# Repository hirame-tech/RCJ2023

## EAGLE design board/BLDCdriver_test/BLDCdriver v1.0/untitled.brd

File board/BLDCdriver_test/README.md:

## issue v1.0
- 1.SPIのSSの未配線
→~~CSをMD基板側でGNDに落として解決(v1.1)~~→SSをD6に配線
- 2.電源コネクタの配線が逆 → 元に戻した(v1.1)

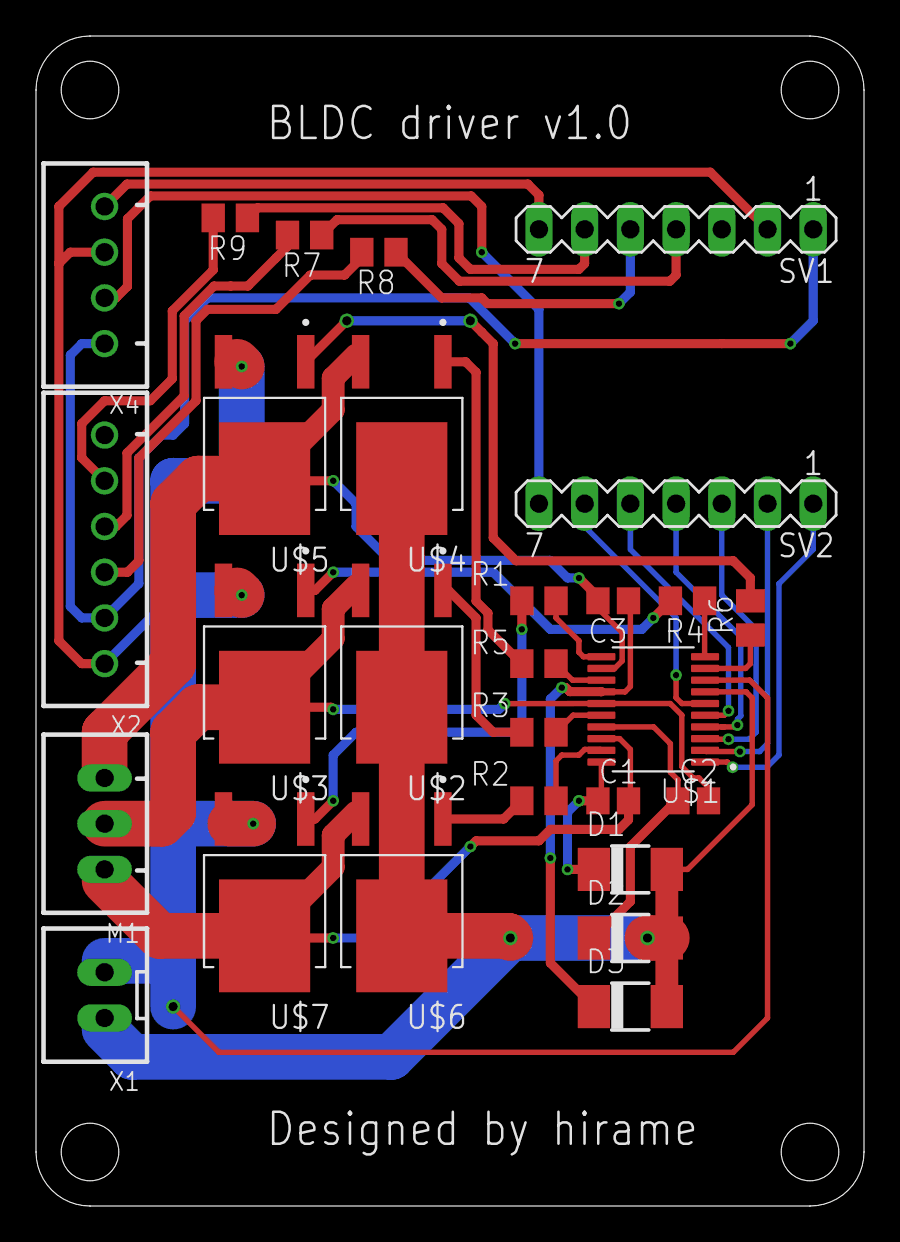
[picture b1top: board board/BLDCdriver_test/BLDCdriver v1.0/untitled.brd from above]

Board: 2 copper layers, 46.0 x 65.0 mm, 28 parts (0 on the bottom side), 35 nets.

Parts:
C1, C2, C3: 1uF; C2012
D1, D2, D3: DO-214AC
M1: JST-XH-03-PIN-LONG-PAD; JST-XH-03-PACKAGE-LONG-PAD
R1, R2, R3, R4, R5, R6: M2012
R7, R8, R9: 300Ω; M2012
SV1, SV2: MA07-1
U$1: DRV8300NIPWR; SOIC65P640X120-20N
U$2, U$3, U$4, U$5, U$6, U$7: H-CHMOSFET; DPAK228P990X238-4N
X1: JST-XH-02-PIN-LONG-PAD; JST-XH-02-PACKAGE-LONG-PAD
X2: JST-XH-06-PIN-ROUND-PAD; JST-XH-06-PACKAGE-ROUND-PAD
X4: JST-XH-04-PIN-ROUND-PAD; JST-XH-04-PACKAGE-ROUND-PAD

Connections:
+5V: SV1.1, X2.2, X4.1
GND: SV1.2, U$1.8, U$3.3, U$5.3, U$7.3, X1.2, X2.1, X4.3
HA: SV2.1, U$1.1
HB: SV2.2, U$1.2
HC: SV2.3, U$1.3
LA: SV2.4, U$1.4
LB: SV2.5, U$1.5
LC: SV2.6, U$1.6
MISO: R8.2, X2.3
MOSI: R7.2, X2.4
unnamed: C2.2, M1.2, U$1.15, U$2.3, U$3.4
unnamed: C3.2, M1.3, U$1.12, U$4.3, U$5.4
unnamed: C1.2, M1.1, U$1.18, U$6.3, U$7.4
unnamed: R2.2, U$6.1
unnamed: R1.2, U$7.1
unnamed: R2.1, U$1.19
unnamed: R1.1, U$1.11
unnamed: R3.2, U$2.1
unnamed: C1.1, D1.C, U$1.20
unnamed: R4.2, U$3.1
unnamed: R7.1, SV1.4
unnamed: R3.1, U$1.16
unnamed: C2.1, D2.C, U$1.17
unnamed: R4.1, U$1.10
unnamed: R6.2, U$5.1
unnamed: R5.2, U$4.1
unnamed: R5.1, U$1.13
unnamed: R6.1, U$1.9
unnamed: C3.1, D3.C, U$1.14
unnamed: R9.1, SV1.6
unnamed: R8.1, SV1.5
RX: SV1.7, X4.4
SCK: R9.2, X2.5
TX: SV2.7, X4.2
VCC: D1.A, D2.A, D3.A, U$1.7, U$2.4, U$4.4, U$6.4, X1.1

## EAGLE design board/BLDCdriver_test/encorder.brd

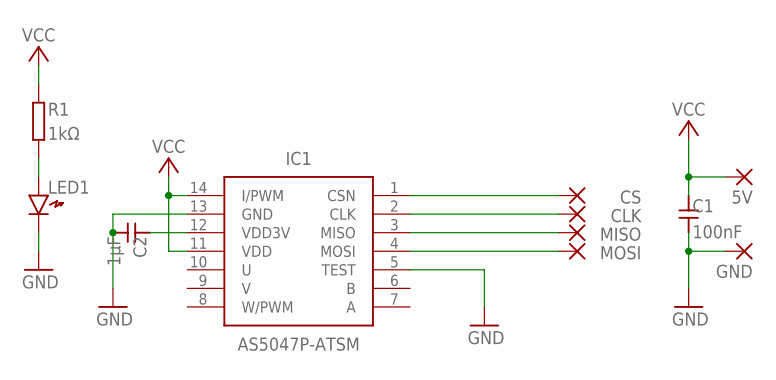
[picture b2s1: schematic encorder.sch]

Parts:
5V: SMD2; SMD1,27-2,54
C1: 100nF; SMD1608
C2: 1µF; SMD1608
CLK: SMD2; SMD1,27-2,54
CS: SMD2; SMD1,27-2,54
GND: SMD2; SMD1,27-2,54
IC1: AS5047P-ATSM; SOP65P640X120-14N
LED1: LED1608
MISO: SMD2; SMD1,27-2,54
MOSI: SMD2; SMD1,27-2,54
R1: 1kΩ; SMD1608

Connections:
GND: C1.2, C2.2, GND.1, IC1.5 (TEST), IC1.13 (GND), LED1.K
unnamed: C2.1, IC1.12 (VDD3V)
unnamed: CS.1, IC1.1 (CSN)
unnamed: CLK.1, IC1.2 (CLK)
unnamed: IC1.3 (MISO), MISO.1
unnamed: IC1.4 (MOSI), MOSI.1
unnamed: LED1.A, R1.2
VCC: 5V.1, C1.1, IC1.11 (VDD), IC1.14 (I/PWM), R1.1

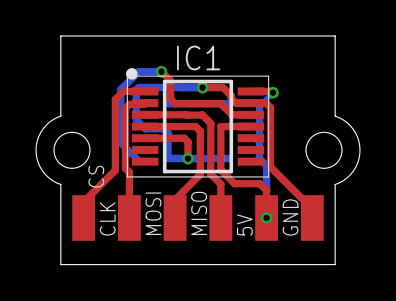
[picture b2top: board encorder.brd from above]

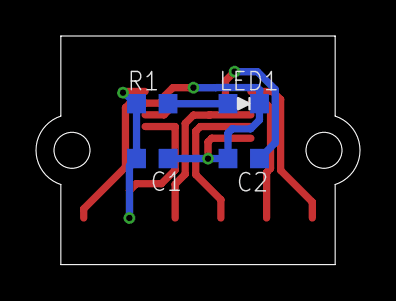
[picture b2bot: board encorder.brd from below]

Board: 2 copper layers, 18.0 x 12.7 mm, 11 parts (4 on the bottom side), 8 nets.

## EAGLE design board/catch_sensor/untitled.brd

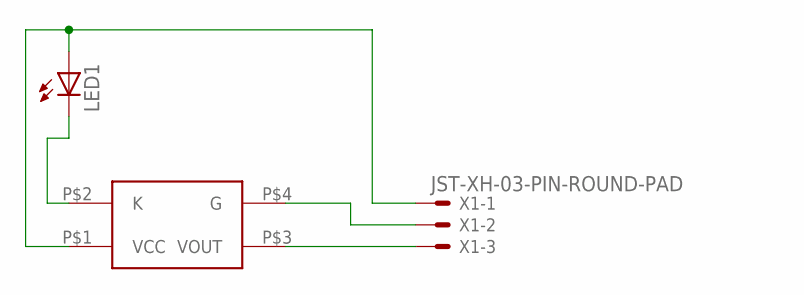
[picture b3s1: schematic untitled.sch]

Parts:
LED1: LED3MM
U$1: S4282-51
X1: JST-XH-03-PIN-ROUND-PAD; JST-XH-03-PACKAGE-ROUND-PAD

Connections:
unnamed: LED1.K (C), U$1.P$2 (K)
unnamed: U$1.P$3 (VOUT), X1.3
unnamed: LED1.A, U$1.P$1 (VCC), X1.1
unnamed: U$1.P$4 (G), X1.2

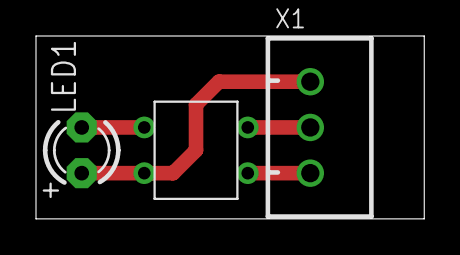
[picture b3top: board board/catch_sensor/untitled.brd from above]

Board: 2 copper layers, 21.6 x 10.2 mm, 3 parts (0 on the bottom side), 4 nets.

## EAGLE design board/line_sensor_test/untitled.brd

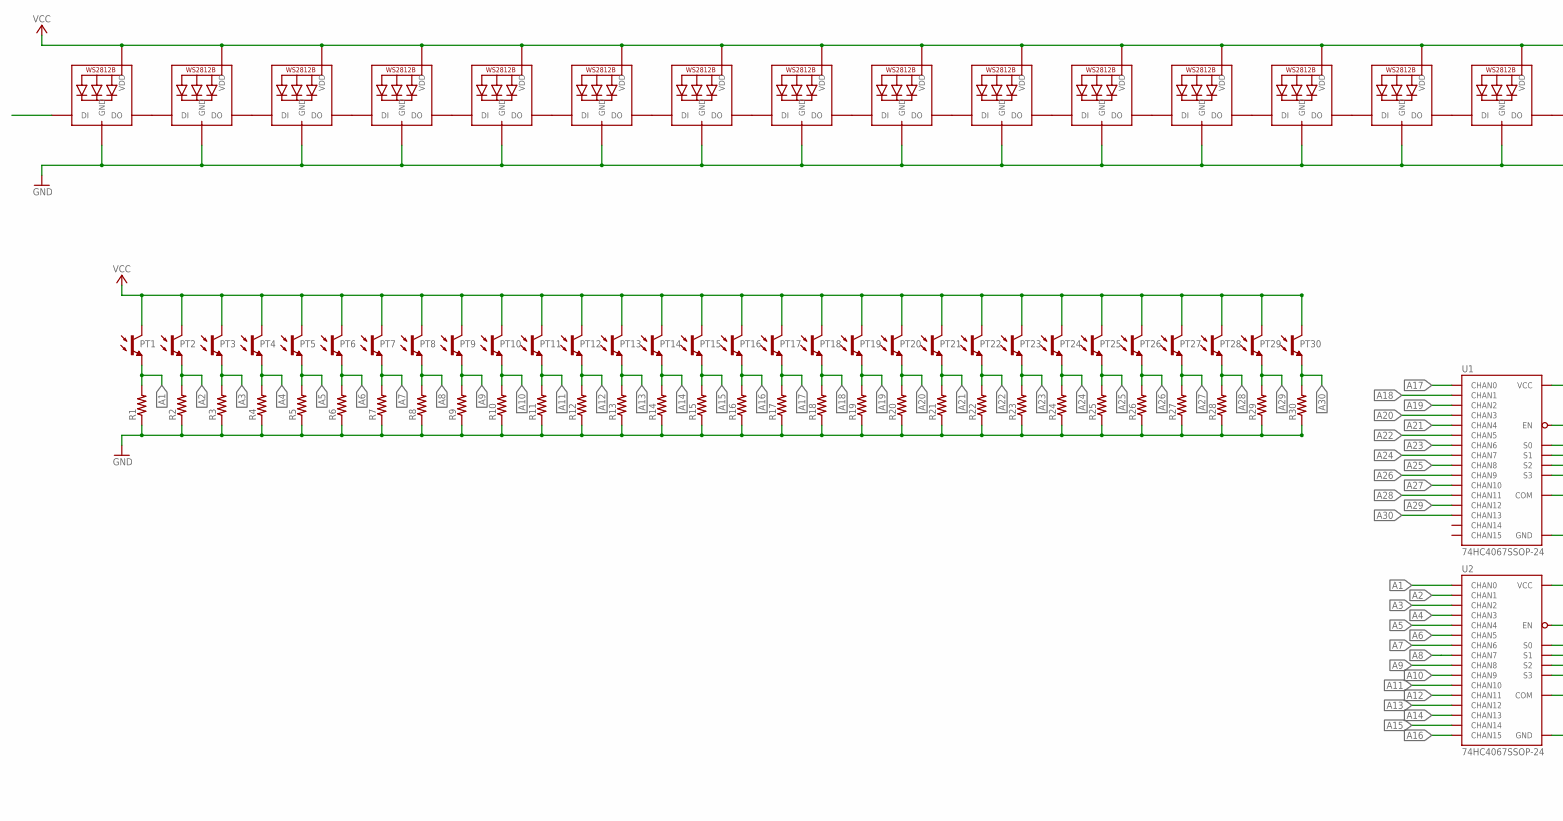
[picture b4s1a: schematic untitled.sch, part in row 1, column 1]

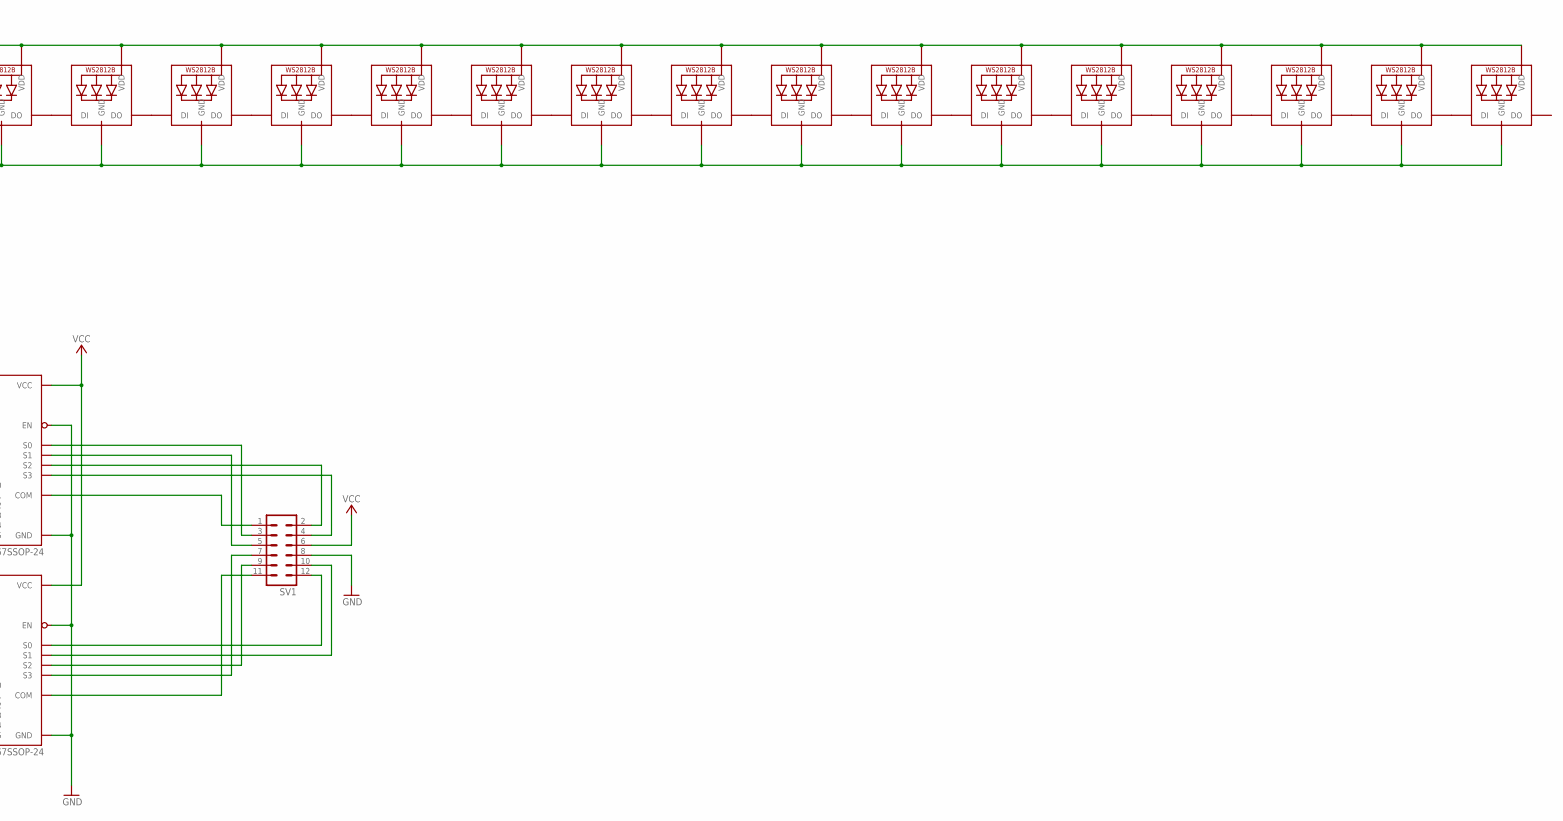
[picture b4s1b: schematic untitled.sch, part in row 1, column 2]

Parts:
LED1, LED2, LED3, LED4, LED5, LED6, LED7, LED8, LED9, LED10, LED11, LED12, LED13, LED14, LED15, LED16, LED17, LED18, LED19, LED20, LED21, LED22, LED23, LED24, LED25, LED26, LED27, LED28, LED29, LED30: WS2812B_5050N; WS2812B-NARROW
PT1, PT2, PT3, PT4, PT5, PT6, PT7, PT8, PT9, PT10, PT11, PT12, PT13, PT14, PT15, PT16, PT17, PT18, PT19, PT20, PT21, PT22, PT23, PT24, PT25, PT26, PT27, PT28, PT29, PT30: TPS611; NJL7502L
R1, R2, R3, R4, R5, R6, R7, R8, R9, R10, R11, R12, R13, R14, R15, R16, R17, R18, R19, R20, R21, R22, R23, R24, R25, R26, R27, R28, R29, R30: R-US_M2012; M2012
SV1: MA06-2
U1, U2: 74HC4067SSOP-24; SSOP24

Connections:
A1: PT1.E, R1.2, U2.9 (CHAN0)
A2: PT2.E, R2.2, U2.8 (CHAN1)
A3: PT3.E, R3.2, U2.7 (CHAN2)
A4: PT4.E, R4.2, U2.6 (CHAN3)
A5: PT5.E, R5.2, U2.5 (CHAN4)
A6: PT6.E, R6.2, U2.4 (CHAN5)
A7: PT7.E, R7.2, U2.3 (CHAN6)
A8: PT8.E, R8.2, U2.2 (CHAN7)
A9: PT9.E, R9.2, U2.23 (CHAN8)
A10: PT10.E, R10.2, U2.22 (CHAN9)
A11: PT11.E, R11.2, U2.21 (CHAN10)
A12: PT12.E, R12.2, U2.20 (CHAN11)
A13: PT13.E, R13.2, U2.19 (CHAN12)
A14: PT14.E, R14.2, U2.18 (CHAN13)
A15: PT15.E, R15.2, U2.17 (CHAN14)
A16: PT16.E, R16.2, U2.16 (CHAN15)
A17: PT17.E, R17.2, U1.9 (CHAN0)
A18: PT18.E, R18.2, U1.8 (CHAN1)
A19: PT19.E, R19.2, U1.7 (CHAN2)
A20: PT20.E, R20.2, U1.6 (CHAN3)
A21: PT21.E, R21.2, U1.5 (CHAN4)
A22: PT22.E, R22.2, U1.4 (CHAN5)
A23: PT23.E, R23.2, U1.3 (CHAN6)
A24: PT24.E, R24.2, U1.2 (CHAN7)
A25: PT25.E, R25.2, U1.23 (CHAN8)
A26: PT26.E, R26.2, U1.22 (CHAN9)
A27: PT27.E, R27.2, U1.21 (CHAN10)
A28: PT28.E, R28.2, U1.20 (CHAN11)
A29: PT29.E, R29.2, U1.19 (CHAN12)
A30: PT30.E, R30.2, U1.18 (CHAN13)
AIN0: SV1.1, U1.1 (COM); also elsewhere on the board
AIN1: SV1.11, U2.1 (COM); also elsewhere on the board
GND: LED1.3-GND (GND), LED2.3-GND (GND), LED3.3-GND (GND), LED4.3-GND (GND), LED5.3-GND (GND), LED6.3-GND (GND), LED7.3-GND (GND), LED8.3-GND (GND), LED9.3-GND (GND), LED10.3-GND (GND), LED11.3-GND (GND), LED12.3-GND (GND), LED13.3-GND (GND), LED14.3-GND (GND), LED15.3-GND (GND), LED16.3-GND (GND), LED17.3-GND (GND), LED18.3-GND (GND), LED19.3-GND (GND), LED20.3-GND (GND), LED21.3-GND (GND), LED22.3-GND (GND), LED23.3-GND (GND), LED24.3-GND (GND), LED25.3-GND (GND), LED26.3-GND (GND), LED27.3-GND (GND), LED28.3-GND (GND), LED29.3-GND (GND), LED30.3-GND (GND), R1.1, R2.1, R3.1, R4.1, R5.1, R6.1, R7.1, R8.1, R9.1, R10.1, R11.1, R12.1, R13.1, R14.1, R15.1, R16.1, R17.1, R18.1, R19.1, R20.1, R21.1, R22.1, R23.1, R24.1, R25.1, R26.1, R27.1, R28.1, R29.1, R30.1, SV1.8, U1.12 (GND), U1.15 (EN), U2.12 (GND), U2.15 (EN); also elsewhere on the board
LED_IN: LED1.4-DIN (DI); also elsewhere on the board
LED_OUT: LED30.2-DOUT (DO); also elsewhere on the board
unnamed: LED1.2-DOUT (DO), LED2.4-DIN (DI)
unnamed: LED2.2-DOUT (DO), LED3.4-DIN (DI)
unnamed: LED3.2-DOUT (DO), LED4.4-DIN (DI)
unnamed: LED4.2-DOUT (DO), LED5.4-DIN (DI)
unnamed: LED6.2-DOUT (DO), LED7.4-DIN (DI)
unnamed 40: SV1.2, U1.14 (S2); also elsewhere on the board
unnamed 41: SV1.4, U1.13 (S3); also elsewhere on the board
unnamed 42: SV1.7, U2.13 (S3); also elsewhere on the board
unnamed 43: SV1.9, U2.14 (S2); also elsewhere on the board
unnamed: LED7.2-DOUT (DO), LED8.4-DIN (DI)
unnamed 45: SV1.10, U2.11 (S1); also elsewhere on the board
unnamed 46: SV1.12, U2.10 (S0); also elsewhere on the board
unnamed 47: SV1.5, U1.11 (S1); also elsewhere on the board
unnamed 48: SV1.3, U1.10 (S0); also elsewhere on the board
unnamed: LED8.2-DOUT (DO), LED9.4-DIN (DI)
unnamed: LED9.2-DOUT (DO), LED10.4-DIN (DI)
unnamed: LED5.2-DOUT (DO), LED6.4-DIN (DI)
unnamed: LED11.2-DOUT (DO), LED12.4-DIN (DI)
unnamed: LED12.2-DOUT (DO), LED13.4-DIN (DI)
unnamed: LED13.2-DOUT (DO), LED14.4-DIN (DI)
unnamed: LED14.2-DOUT (DO), LED15.4-DIN (DI)
unnamed: LED10.2-DOUT (DO), LED11.4-DIN (DI)
unnamed: LED16.2-DOUT (DO), LED17.4-DIN (DI)
unnamed: LED17.2-DOUT (DO), LED18.4-DIN (DI)
unnamed: LED18.2-DOUT (DO), LED19.4-DIN (DI)
unnamed: LED19.2-DOUT (DO), LED20.4-DIN (DI)
unnamed: LED15.2-DOUT (DO), LED16.4-DIN (DI)
unnamed: LED21.2-DOUT (DO), LED22.4-DIN (DI)
unnamed: LED22.2-DOUT (DO), LED23.4-DIN (DI)
unnamed: LED23.2-DOUT (DO), LED24.4-DIN (DI)
unnamed: LED24.2-DOUT (DO), LED25.4-DIN (DI)
unnamed: LED20.2-DOUT (DO), LED21.4-DIN (DI)
unnamed: LED26.2-DOUT (DO), LED27.4-DIN (DI)
unnamed: LED27.2-DOUT (DO), LED28.4-DIN (DI)
unnamed: LED28.2-DOUT (DO), LED29.4-DIN (DI)
unnamed: LED29.2-DOUT (DO), LED30.4-DIN (DI)
unnamed: LED25.2-DOUT (DO), LED26.4-DIN (DI)
VCC: LED1.1-VDD (VDD), LED2.1-VDD (VDD), LED3.1-VDD (VDD), LED4.1-VDD (VDD), LED5.1-VDD (VDD), LED6.1-VDD (VDD), LED7.1-VDD (VDD), LED8.1-VDD (VDD), LED9.1-VDD (VDD), LED10.1-VDD (VDD), LED11.1-VDD (VDD), LED12.1-VDD (VDD), LED13.1-VDD (VDD), LED14.1-VDD (VDD), LED15.1-VDD (VDD), LED16.1-VDD (VDD), LED17.1-VDD (VDD), LED18.1-VDD (VDD), LED19.1-VDD (VDD), LED20.1-VDD (VDD), LED21.1-VDD (VDD), LED22.1-VDD (VDD), LED23.1-VDD (VDD), LED24.1-VDD (VDD), LED25.1-VDD (VDD), LED26.1-VDD (VDD), LED27.1-VDD (VDD), LED28.1-VDD (VDD), LED29.1-VDD (VDD), LED30.1-VDD (VDD), PT1.C, PT2.C, PT3.C, PT4.C, PT5.C, PT6.C, PT7.C, PT8.C, PT9.C, PT10.C, PT11.C, PT12.C, PT13.C, PT14.C, PT15.C, PT16.C, PT17.C, PT18.C, PT19.C, PT20.C, PT21.C, PT22.C, PT23.C, PT24.C, PT25.C, PT26.C, PT27.C, PT28.C, PT29.C, PT30.C, SV1.6, U1.24 (VCC), U2.24 (VCC); also elsewhere on the board

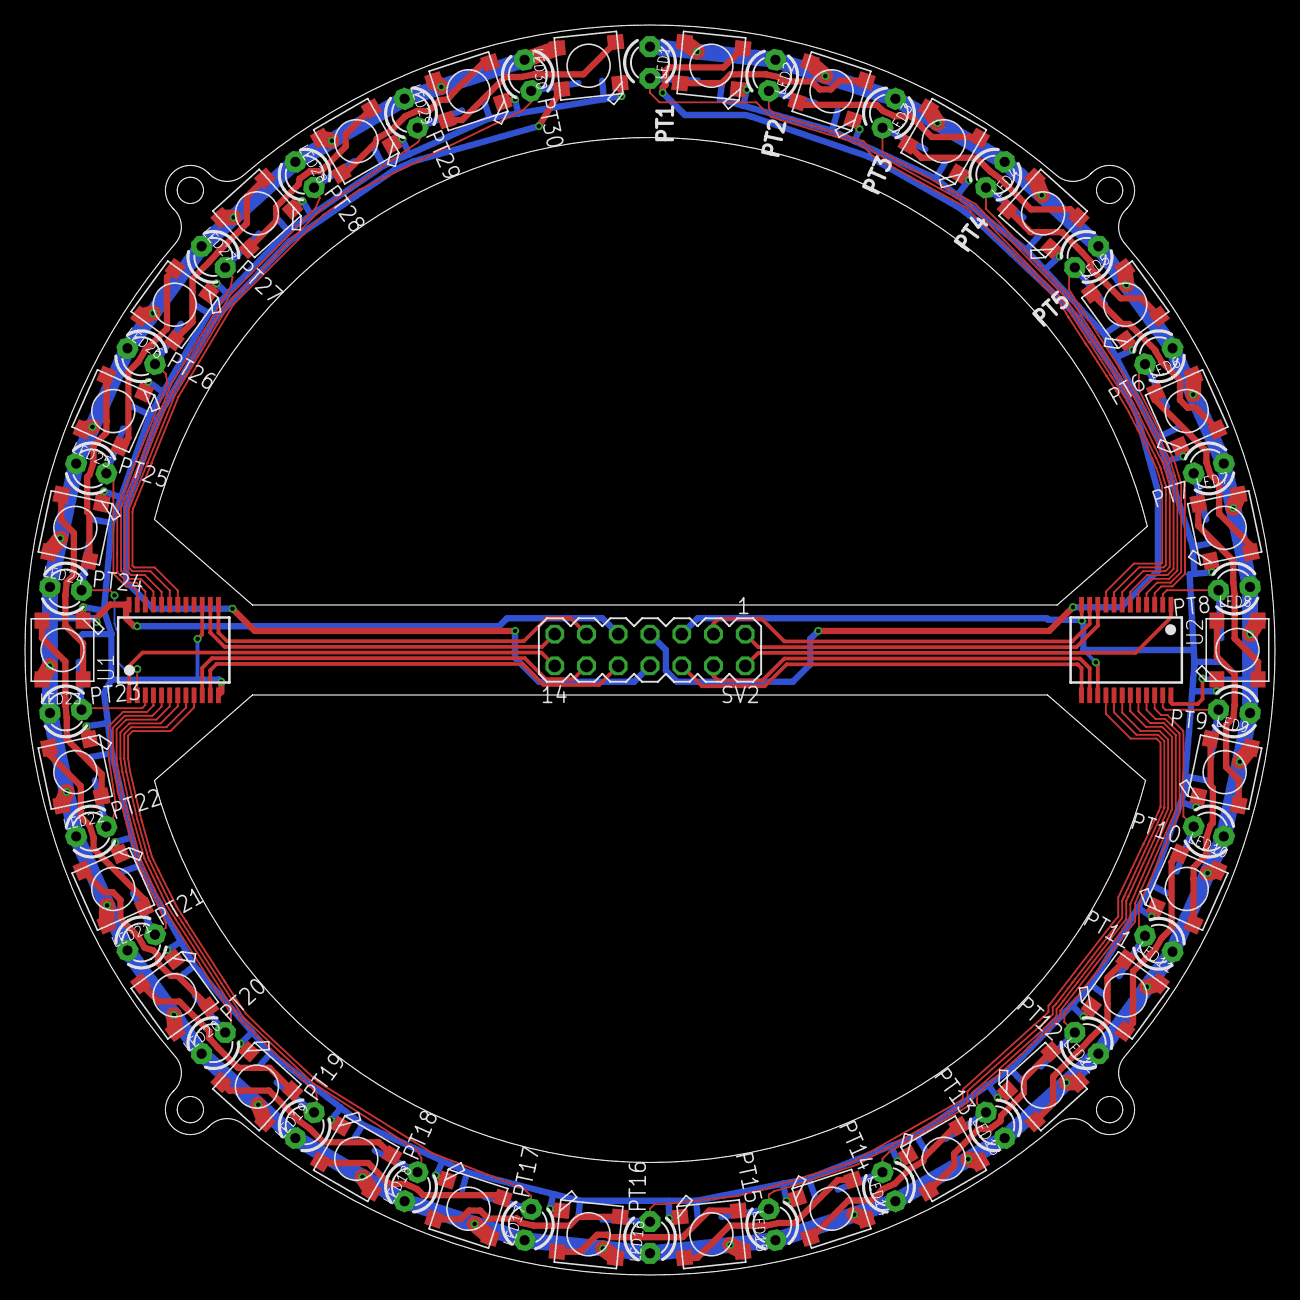
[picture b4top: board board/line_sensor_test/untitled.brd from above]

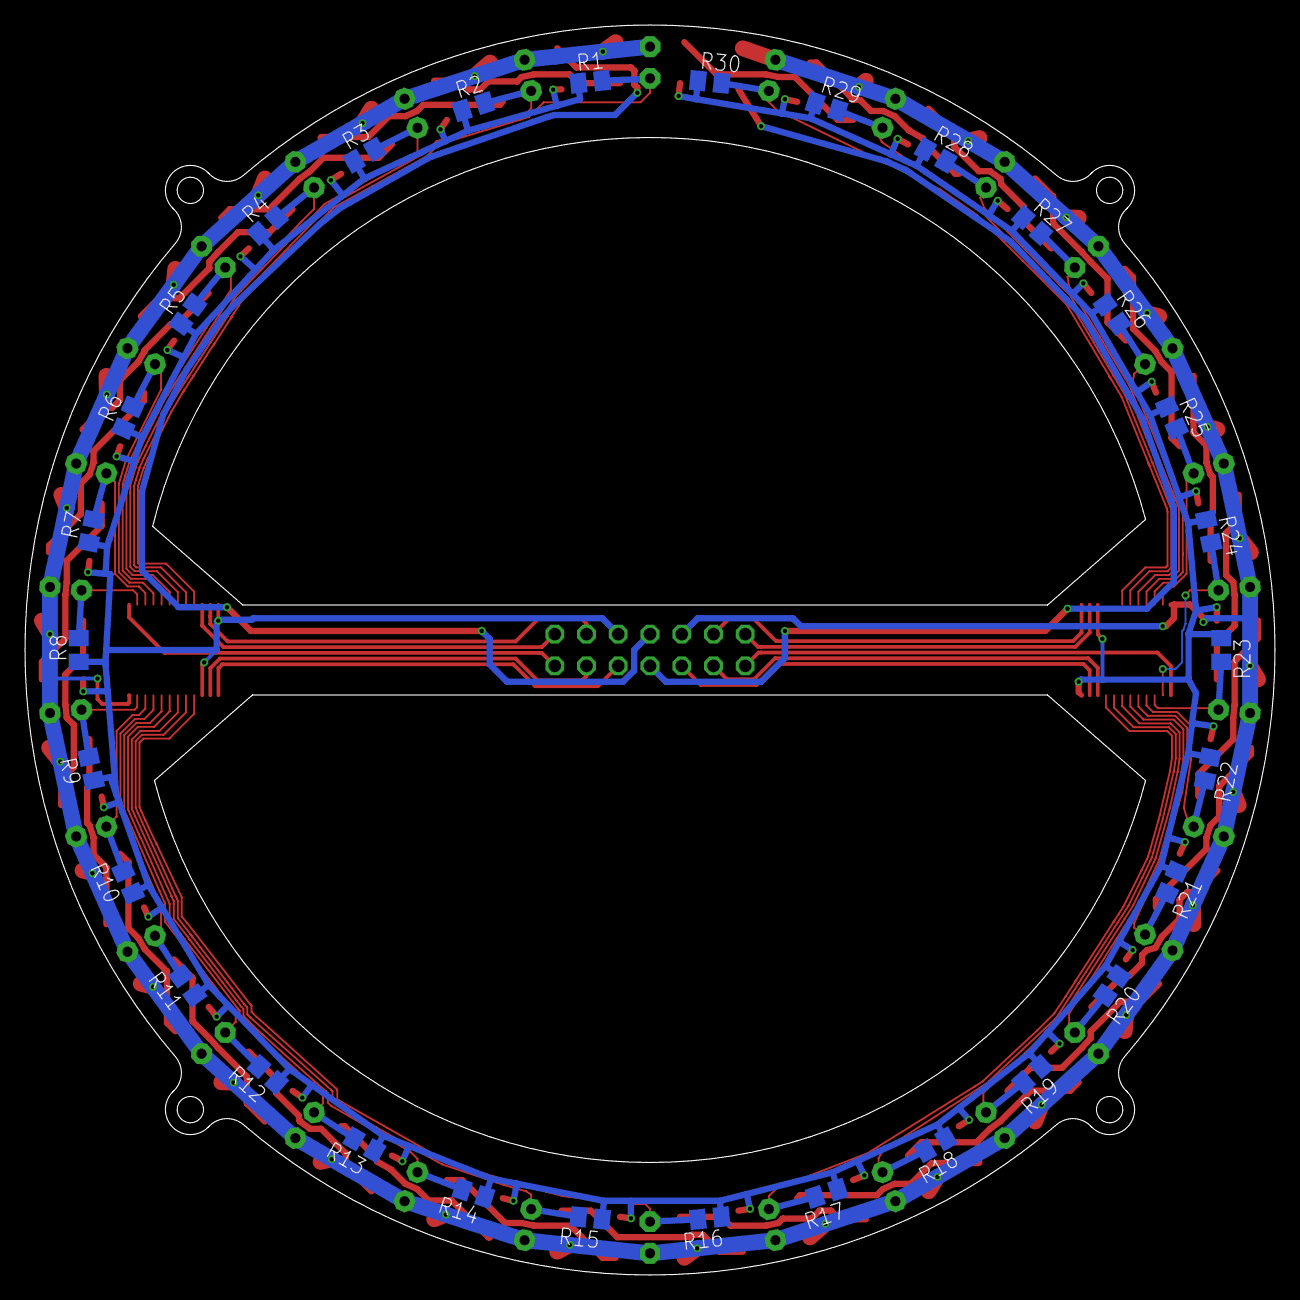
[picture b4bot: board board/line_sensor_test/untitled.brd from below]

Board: 2 copper layers, 100.0 x 100.0 mm, 93 parts (30 on the bottom side), 73 nets.

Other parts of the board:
SV2: MA07-2

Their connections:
AIN0: SV2.14; also elsewhere on the board
AIN1: SV2.2; also elsewhere on the board
GND: SV2.5; also elsewhere on the board
LED_IN: SV2.7; also elsewhere on the board
LED_OUT: SV2.8; also elsewhere on the board
unnamed 40: SV2.13; also elsewhere on the board
unnamed 41: SV2.11; also elsewhere on the board
unnamed 42: SV2.6; also elsewhere on the board
unnamed 43: SV2.4; also elsewhere on the board
unnamed 45: SV2.3; also elsewhere on the board
unnamed 46: SV2.1; also elsewhere on the board
unnamed 47: SV2.10; also elsewhere on the board
unnamed 48: SV2.12; also elsewhere on the board
VCC: SV2.9; also elsewhere on the board

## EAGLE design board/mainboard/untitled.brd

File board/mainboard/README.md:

#v1 isuue
 - RCフィルタのコンデンサがin側についている(out側にないといけない)

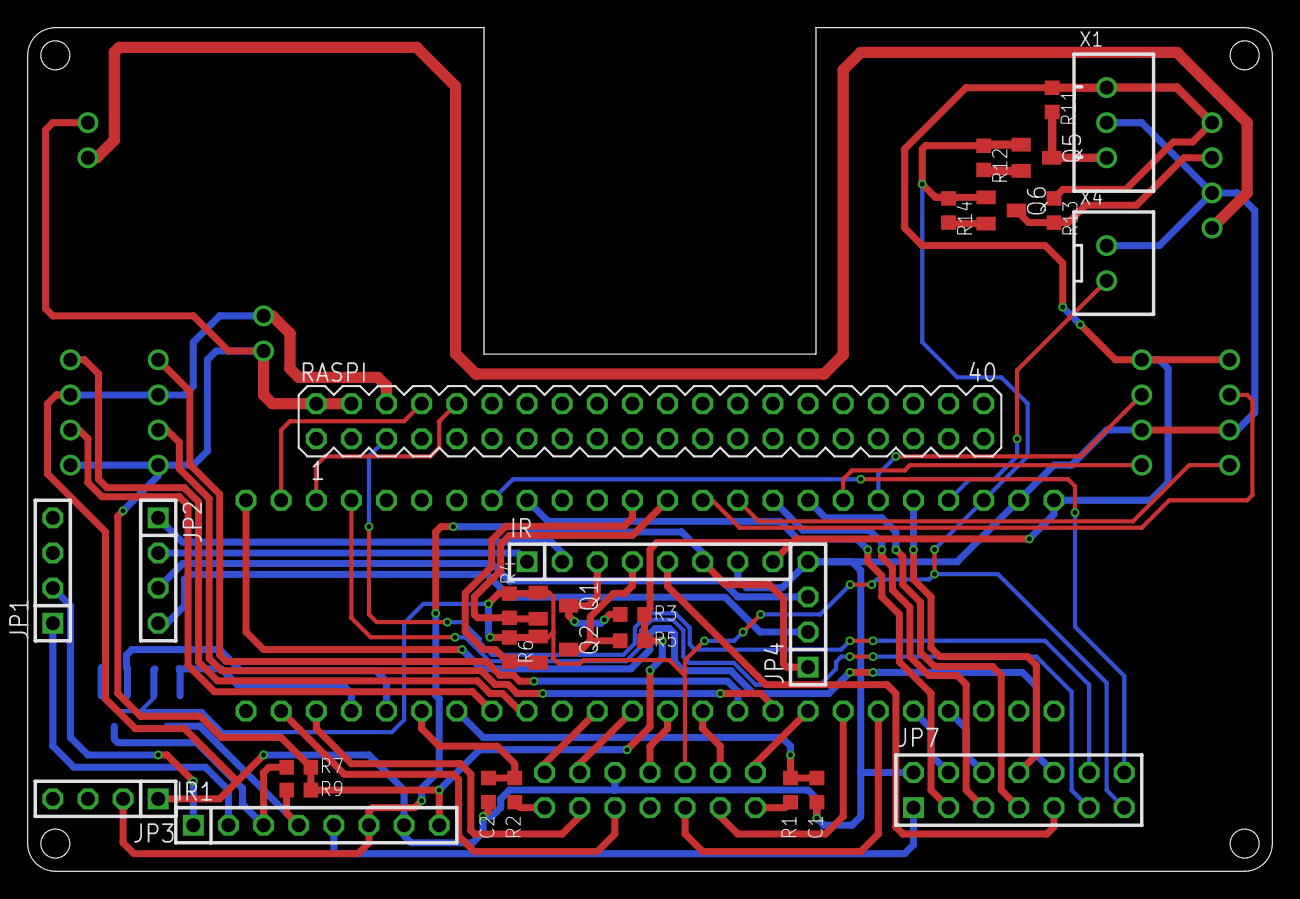
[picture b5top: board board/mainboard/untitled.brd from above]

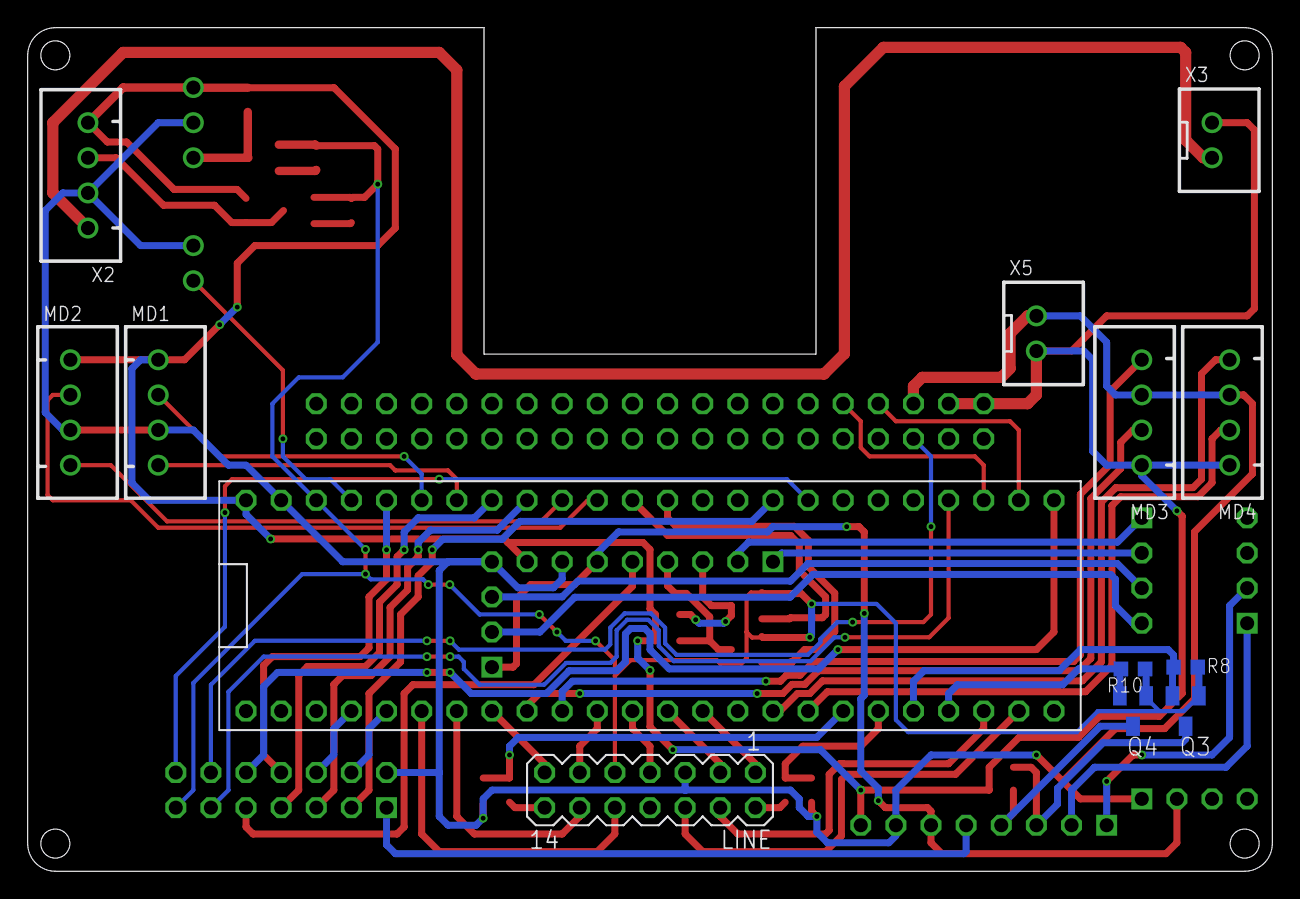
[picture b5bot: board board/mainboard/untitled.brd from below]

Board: 2 copper layers, 90.0 x 61.0 mm, 41 parts (13 on the bottom side), 59 nets.

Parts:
C1, C2: SMD1608
IR, IR1: 1X08
JP1, JP2, JP3, JP4: 1X04
JP7: 2X07
LINE: MA07-2
MD1, MD2, MD3, MD4: JST-XH; JST-XH-04-PACKAGE-ROUND-PAD
Q1, Q2, Q3, Q4, Q5, Q6: SOT23
R1, R2, R3, R4, R5, R6, R7, R8, R9, R10, R11, R12, R13, R14: SMD1608
RASPI: MA20-2
U$1: TEENSY4.1
X1: JST-XH-03-PIN-ROUND-PAD; JST-XH-03-PACKAGE-ROUND-PAD
X2: JST-XH-04-PIN-ROUND-PAD; JST-XH-04-PACKAGE-ROUND-PAD
X3, X4, X5: JST-XH-02-PIN-ROUND-PAD; JST-XH-02-PACKAGE-ROUND-PAD

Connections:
+3V3: JP7.13, LINE.9, Q1.1, Q2.1, Q3.1, Q4.1, Q5.1, Q6.1, R4.1, R6.1, R8.1, R10.1, R12.1, R14.1, U$1.P$11
+5V: IR.8, IR1.8, MD1.1, MD2.1, MD3.1, MD4.1, R3.1, R5.1, R7.1, R9.1, R11.1, R13.1, RASPI.2, RASPI.4, U$1.P$13, X1.1, X2.4, X3.1, X5.2
CAM_RX: RASPI.10, U$1.P$39
CAM_TX: RASPI.8, U$1.P$38
CATCH_1: Q5.2, R12.2
CATCH_2: Q6.2, R14.2
GND: C1.2, C2.2, IR.7, IR1.7, JP3.1, JP4.4, JP7.2, LINE.5, MD1.3, MD2.3, MD3.3, MD4.3, RASPI.6, U$1.P$12, X1.2, X2.2, X4.1, X5.1
GYRO_D+: IR1.2, JP1.1
GYRO_D-: IR1.1, JP1.2
GYRO_RESET: IR1.5, JP7.1
GYRO_RX: Q4.2, R10.2, U$1.P$33
GYRO_TX: Q3.2, R8.2, U$1.P$32
IR_D+: IR.2, JP2.1
IR_D-: IR.1, JP2.2
IR_RESET: IR.5, JP7.9
IR_RX: Q2.2, R6.2, U$1.P$48
IR_TX: Q1.2, R4.2, U$1.P$2
KICK: U$1.P$10, X4.2
LED1: JP7.4, U$1.P$20
LED2: JP7.6, U$1.P$21
LED3: JP7.5, U$1.P$5
LED4: JP7.7, U$1.P$6
LED5: JP7.8, U$1.P$9
LED6: JP7.10, U$1.P$37
LINE_A1: C1.1, R1.1, U$1.P$30
LINE_A2: C2.1, R2.1, U$1.P$31
LINE_LED: LINE.7, U$1.P$1
LINE_S10: LINE.12, U$1.P$18
LINE_S11: LINE.10, U$1.P$19
LINE_S12: LINE.13, U$1.P$17
LINE_S13: LINE.11, U$1.P$14
LINE_S20: LINE.1, U$1.P$26
LINE_S21: LINE.3, U$1.P$25
LINE_S22: LINE.4, U$1.P$34
LINE_S23: LINE.6, U$1.P$35
MAIN_RESET: JP7.11, U$1.P$40
MD1_RX: MD1.4, U$1.P$7
MD1_TX: MD1.2, U$1.P$8
MD2_RX: MD2.4, U$1.P$4
MD2_TX: MD2.2, U$1.P$3
MD3_RX: MD3.4, U$1.P$15
MD3_TX: MD3.2, U$1.P$16
MD4_RX: MD4.4, U$1.P$28
MD4_TX: MD4.2, U$1.P$29
unnamed: IR1.3, Q3.3, R7.2
unnamed: LINE.14, R1.2
unnamed: LINE.2, R2.2
unnamed: IR.3, Q1.3, R3.2
unnamed: IR1.4, Q4.3, R9.2
unnamed: IR.4, Q2.3, R5.2
unnamed: Q6.3, R13.2, X2.3
unnamed: X2.1, X3.2
unnamed: Q5.3, R11.2, X1.3
unnamed: JP2.4, JP4.2
unnamed: JP2.3, JP4.3
RASPI_RESET: JP7.12, RASPI.5
SWITCH: JP7.3, U$1.P$45
TRIM: JP7.14, U$1.P$44
UVCC: IR.6, IR1.6, JP3.2, JP4.1
